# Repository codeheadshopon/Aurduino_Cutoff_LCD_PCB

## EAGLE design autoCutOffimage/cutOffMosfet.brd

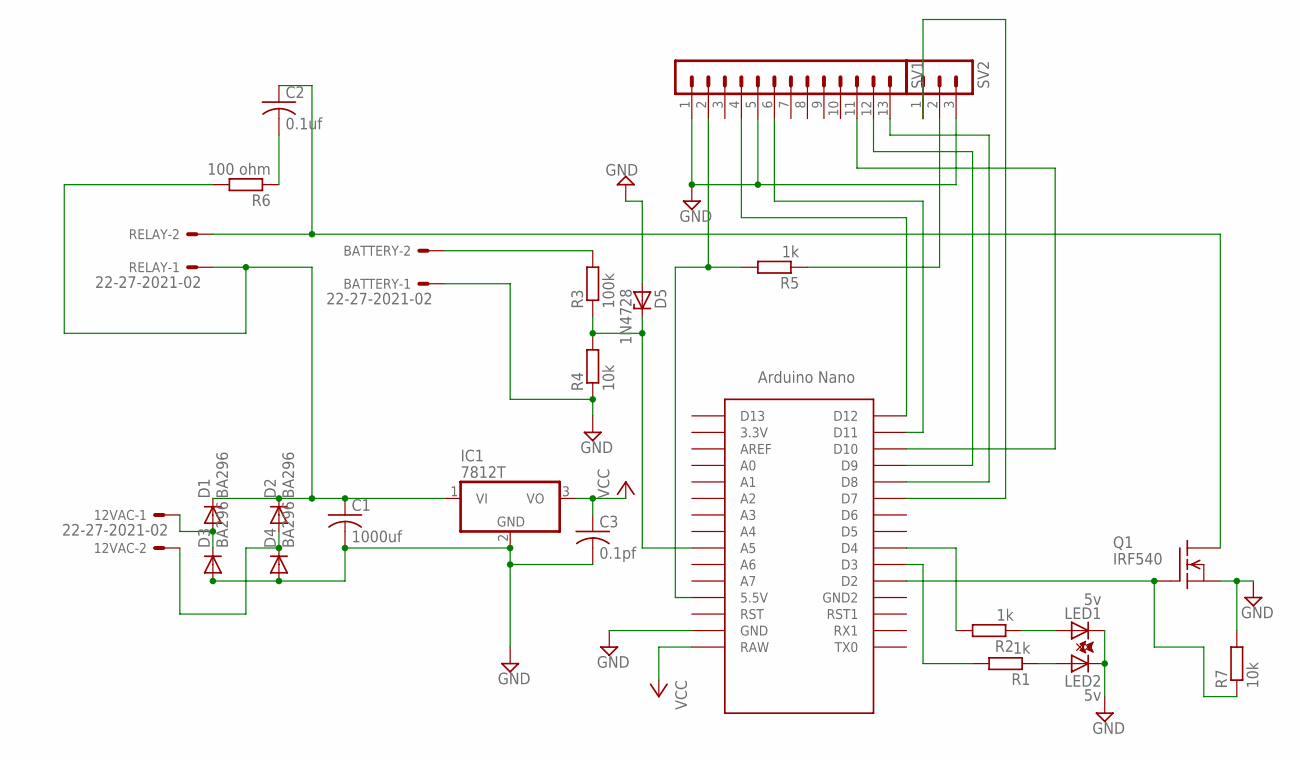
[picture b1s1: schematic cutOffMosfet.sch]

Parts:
12VAC: 22-27-2021-02; 6410-02
BATTERY: 22-27-2021-02; 6410-02
C1: 1000uf; C050-025X075
C2: 0.1uf; C050-025X075
C3: 0.1pf; C050-025X075
D1, D2, D3, D4: BA296; P2-15
D5: 1N4728; DO41Z10
IC1: 7812T; TO220H
LED1, LED2: 5v; LED5MM
Q1: IRF540; TO220
R1, R2, R5: 1k; 0207/10
R3: 100k; 0207/10
R4, R7: 10k; 0207/10
R6: 100 ohm; 0207/10
RELAY: 22-27-2021-02; 6410-02
SV1: MA13-1
SV2: MA03-1
U$1: NANO

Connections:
GND: BATTERY.1, C1.2, C3.2, D3.A, D4.A, D5.A, IC1.2 (GND), LED1.K (C), LED2.K (C), Q1.3 (S), R4.1, R7.2, SV1.1, SV1.5, SV2.3, U$1.GND
unnamed: C2.1, Q1.2 (D), RELAY.2
unnamed: R1.2, U$1.D3
unnamed: R2.2, U$1.D4
unnamed: BATTERY.2, R3.2
unnamed: 12VAC.1, D1.A, D3.C
unnamed: 12VAC.2, D2.A, D4.C
unnamed: SV1.6, U$1.D11
unnamed: LED2.A, R1.1
unnamed: LED1.A, R2.1
unnamed: SV1.11, U$1.D10
unnamed: Q1.1 (G), R7.1, U$1.D2
unnamed: SV1.12, U$1.D9
unnamed: D5.C, R3.1, R4.2, U$1.A5
unnamed: R5.1, SV2.2
unnamed: SV1.4, U$1.D12
unnamed: SV1.13, U$1.D8
unnamed: C1.1, D1.C, D2.C, IC1.1 (VI), R6.2, RELAY.1
unnamed: SV2.1, U$1.D7
unnamed: R5.2, SV1.2, U$1.5V (5.5V)
unnamed: C2.2, R6.1
VCC: C3.1, IC1.3 (VO), U$1.RAW

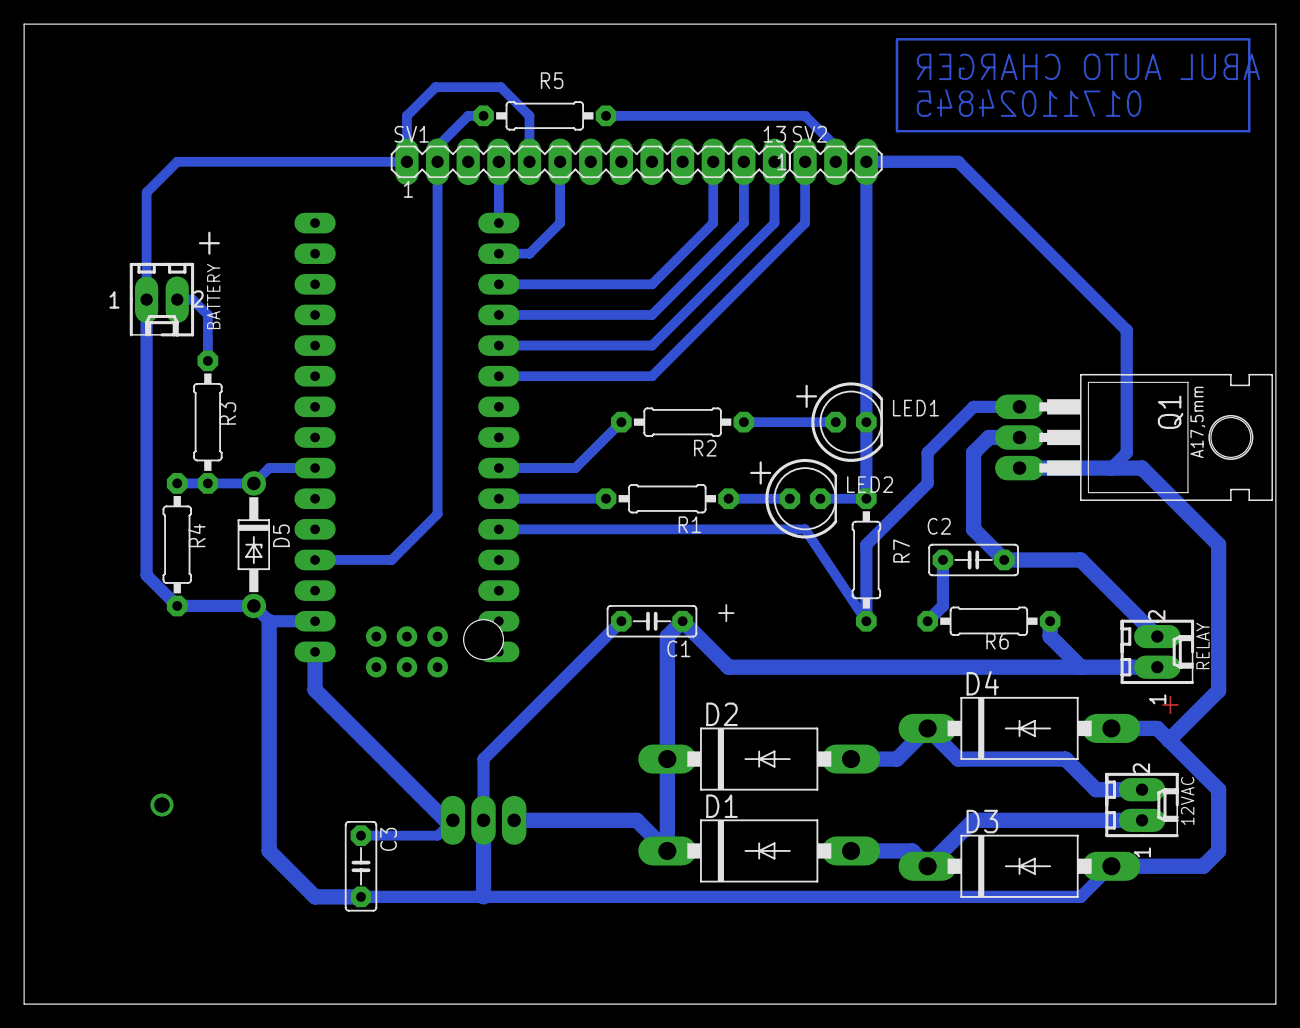
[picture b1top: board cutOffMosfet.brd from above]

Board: 2 copper layers, 103.8 x 81.3 mm, 25 parts (1 on the bottom side), 22 nets.

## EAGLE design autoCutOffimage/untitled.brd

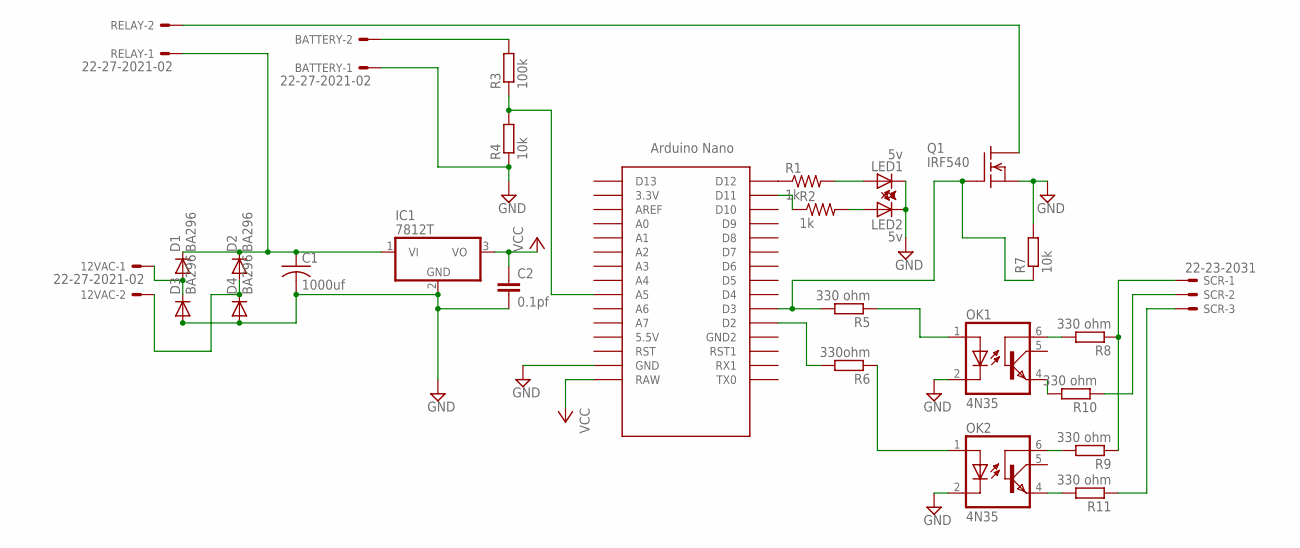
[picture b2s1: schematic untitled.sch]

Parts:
12VAC: 22-27-2021-02; 6410-02
BATTERY: 22-27-2021-02; 6410-02
C1: 1000uf; C050-025X075
C2: 0.1pf; C7.5B4
D1, D2, D3, D4: BA296; P2-15
IC1: 7812T; TO220H
LED1, LED2: 5v; LED_1206
OK1, OK2: 4N35; DIL06
Q1: IRF540; TO220
R1, R2: 1k; 0207/2V
R3: 100k; 0207/10
R4, R7: 10k; 0207/10
R5, R8, R9, R10, R11: 330 ohm; 0207/10
R6: 330ohm; 0207/10
RELAY: 22-27-2021-02; 6410-02
SCR: 22-23-2031
U$1: NANO

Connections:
GND: BATTERY.1, C1.2, C2.2, D3.A, D4.A, IC1.2 (GND), LED1.C, LED2.C, OK1.2 (C), OK2.2 (C), Q1.3 (S), R4.1, R7.2, U$1.GND
unnamed: R10.1, SCR.2
unnamed: R6.2, U$1.D2
unnamed: BATTERY.2, R3.2
unnamed: 12VAC.1, D1.A, D3.C
unnamed: 12VAC.2, D2.A, D4.C
unnamed: R1.1, U$1.D12
unnamed: LED2.A, R2.2
unnamed: LED1.A, R1.2
unnamed: R2.1, U$1.D11
unnamed: Q1.1 (G), R5.2, R7.1, U$1.D3
unnamed: OK1.1 (A), R5.1
unnamed: R3.1, R4.2, U$1.A5
unnamed: OK2.1 (A), R6.1
unnamed: Q1.2 (D), RELAY.2
unnamed: C1.1, D1.C, D2.C, IC1.1 (VI), RELAY.1
unnamed: R11.1, SCR.3
unnamed: OK1.4 (EMI), R10.2
unnamed: R8.1, R9.1, SCR.1
unnamed: OK1.6 (BAS), R8.2
unnamed: OK2.6 (BAS), R9.2
unnamed: OK2.4 (EMI), R11.2
VCC: C2.1, IC1.3 (VO), U$1.RAW

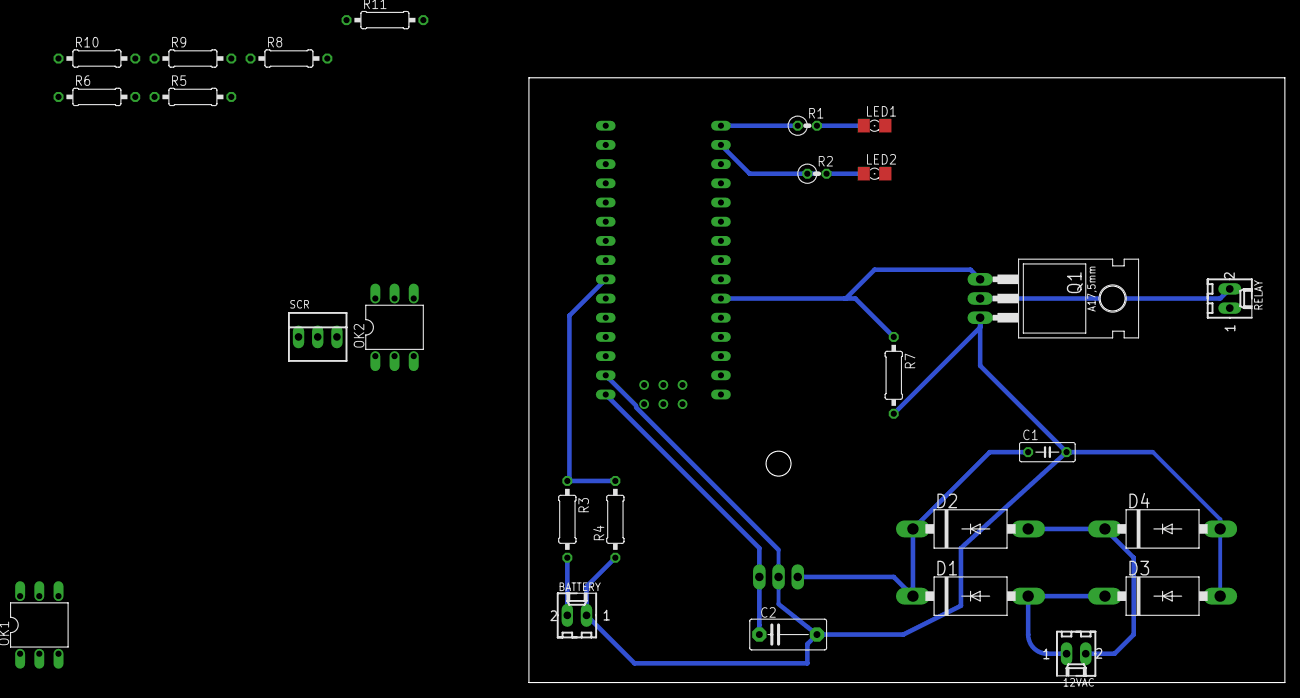
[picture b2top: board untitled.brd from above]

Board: 2 copper layers, 100.0 x 80.0 mm, 28 parts (1 on the bottom side), 23 nets.

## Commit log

2017-07-21 Initial Code
2017-07-21 ImageFileAdded
